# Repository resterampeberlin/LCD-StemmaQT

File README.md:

# Purpose

# Credits

This open source code project is has been proudfully produced in Berlin (and other places around the globe) by

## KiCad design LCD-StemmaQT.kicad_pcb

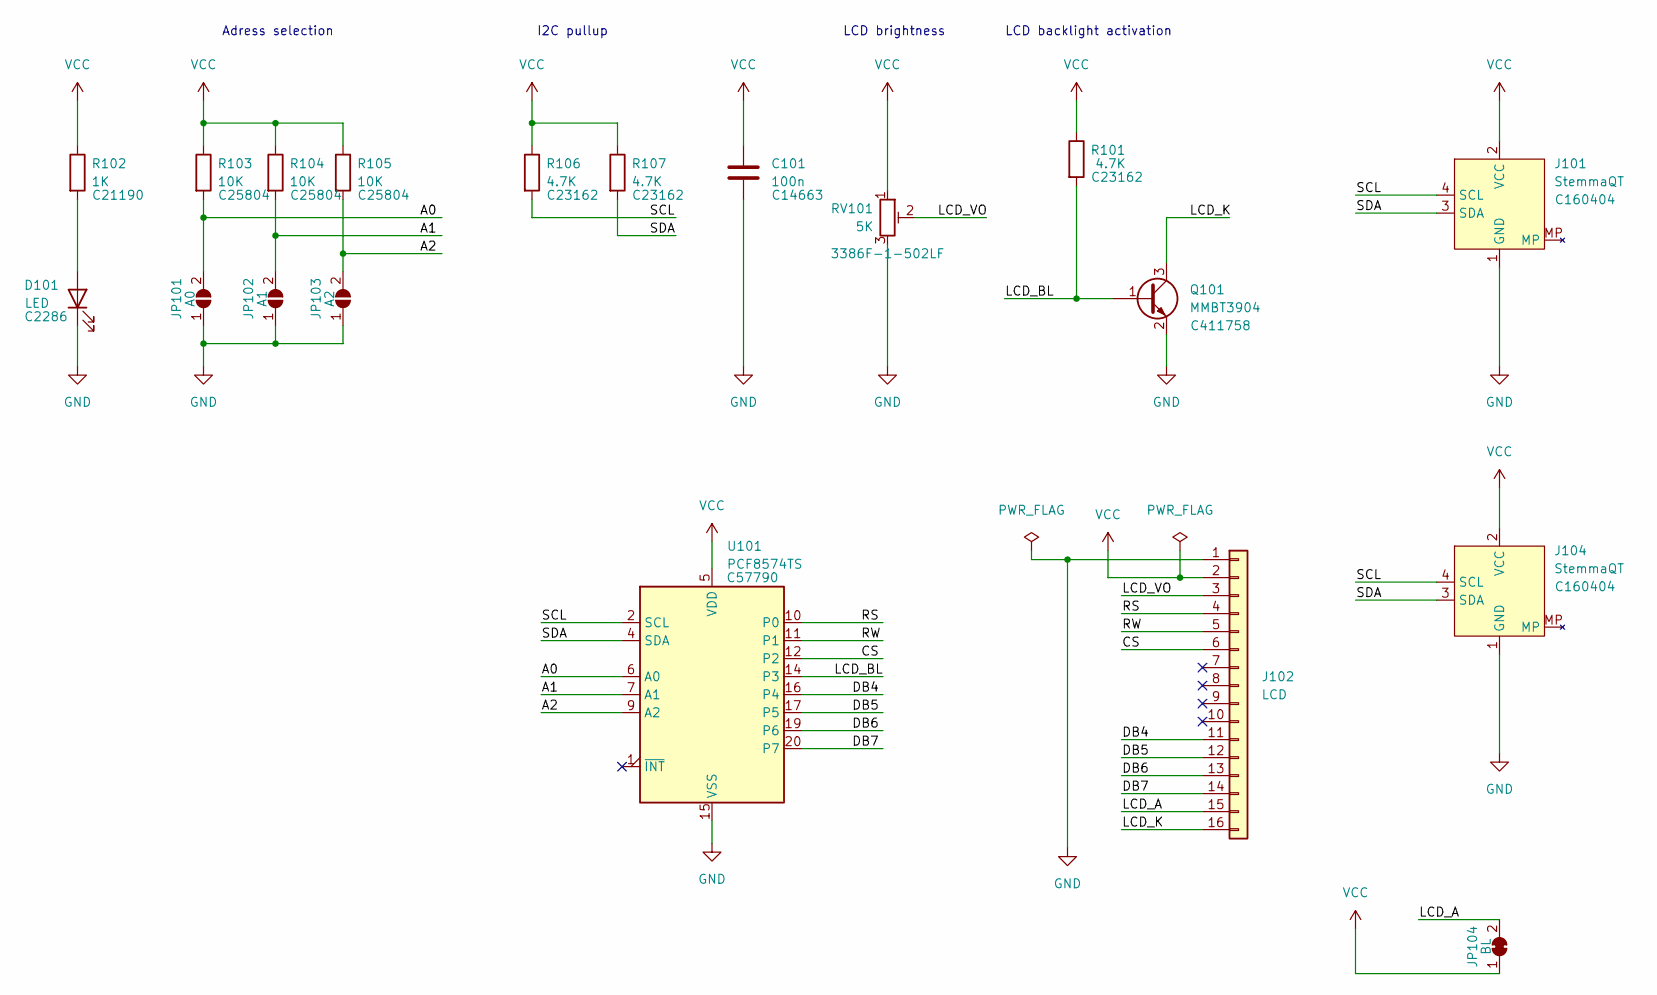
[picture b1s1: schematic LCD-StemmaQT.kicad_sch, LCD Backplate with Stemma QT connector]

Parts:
C101: 100n; C_0603_1608Metric_Pad1.08x0.95mm_HandSolder; LCSC C14663
D101: LED; LED_0603_1608Metric_Pad1.05x0.95mm_HandSolder; LCSC C2286
J101, J104: StemmaQT; JST_SH_SM04B-SRSS-TB_1x04-1MP_P1.00mm_Horizontal; LCSC C160404
J102: LCD; PinHeader_1x16_P2.54mm_Vertical
JP101: A0; SolderJumper-2_P1.3mm_Open_TrianglePad1.0x1.5mm
JP102: A1; SolderJumper-2_P1.3mm_Open_TrianglePad1.0x1.5mm
JP103: A2; SolderJumper-2_P1.3mm_Open_TrianglePad1.0x1.5mm
JP104: BL; SolderJumper-2_P1.3mm_Bridged_Pad1.0x1.5mm
Q101: MMBT3904; SOT-23; LCSC C411758
R101, R106, R107: 4.7K; R_0603_1608Metric_Pad0.98x0.95mm_HandSolder; LCSC C23162
R102: 1K; R_0603_1608Metric_Pad0.98x0.95mm_HandSolder; LCSC C21190
R103, R104, R105: 10K; R_0603_1608Metric_Pad0.98x0.95mm_HandSolder; LCSC C25804
RV101: 5K; Potentiometer_Bourns_3386F_Vertical; DigiKey 3386F-1-502LF
U101: PCF8574TS; SSOP-20_4.4x6.5mm_P0.65mm; LCSC C57790

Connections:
/A0: JP101.2 (B), R103.2, U101.6 (A0)
/A1: JP102.2 (B), R104.2, U101.7 (A1)
/A2: JP103.2 (B), R105.2, U101.9 (A2)
/CS: J102.6, U101.12 (P2)
/DB4: J102.11, U101.16 (P4)
/DB5: J102.12, U101.17 (P5)
/DB6: J102.13, U101.19 (P6)
/DB7: J102.14, U101.20 (P7)
/LCD_A: J102.15, JP104.2 (B)
/LCD_BL: Q101.1 (B), R101.2, U101.14 (P3)
/LCD_K: J102.16, Q101.3 (C)
/LCD_VO: J102.3, RV101.2
/RS: J102.4, U101.10 (P0)
/RW: J102.5, U101.11 (P1)
/SCL: J101.4 (SCL), J104.4 (SCL), R106.2, U101.2 (SCL)
/SDA: J101.3 (SDA), J104.3 (SDA), R107.2, U101.4 (SDA)
GND: C101.2, D101.1 (K), J101.1 (GND), J102.1, J104.1 (GND), JP101.1 (A), JP102.1 (A), JP103.1 (A), Q101.2 (E), RV101.3, U101.15 (VSS)
unnamed: D101.2 (A), R102.2
VCC: C101.1, J101.2 (VCC), J102.2, J104.2 (VCC), JP104.1 (A), R101.1, R102.1, R103.1, R104.1, R105.1, R106.1, R107.1, RV101.1, U101.5 (VDD)

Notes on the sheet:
Adress selection
LCD brightness
LCD backlight activation
I2C pullup

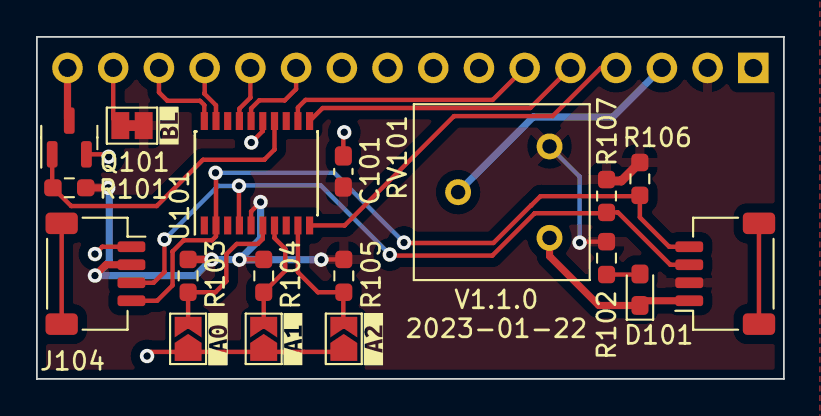
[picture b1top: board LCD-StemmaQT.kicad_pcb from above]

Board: 2 copper layers, 41.5 x 19.0 mm, 23 parts (1 on the bottom side), 19 nets.

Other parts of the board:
kibuzzard-63CD50DB: G***; kibuzzard-63CD50DB
kibuzzard-63CD512B: G***; kibuzzard-63CD512B
kibuzzard-63CD5133: G***; kibuzzard-63CD5133
kibuzzard-63CD5139: G***; kibuzzard-63CD5139

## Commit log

2022-12-23 Production
2022-12-23 Non functional corrections on PCB
2023-01-05 added StemmaQT logo on PCB
2023-01-09 Stemma QT footprint corrected
2023-01-21 Documentation updated
2023-01-22 Added second StemmaQT port

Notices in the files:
LCD-StemmaQT.kicad_pcb:
https://creativecommons.org/licenses/by-nc/4.0
License CC BY-NC 4.0
